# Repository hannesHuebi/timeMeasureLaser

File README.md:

# timeMeasureLaser
This is a repository for a time measuring device based on a laser and fotodiodes. This device was meant to measure the time small model boats needs to go 25m in a towing tank.

In this repository the Schematics and PCB design for the Arduinoshield is given as necessary Hardware for the time measuring equipment.

Additionaly the Arduino code is given which measures the time and provides the commands for the serial interface. 

Based on serial communication an excel-addin is is made which reads out the time and posts it in the excel-sheet. This ribbon/addin is availeble over COM-Interop to use it somerwhere else. This is mainly done to have an interface to VBA to generate buttons to start the time measuring.

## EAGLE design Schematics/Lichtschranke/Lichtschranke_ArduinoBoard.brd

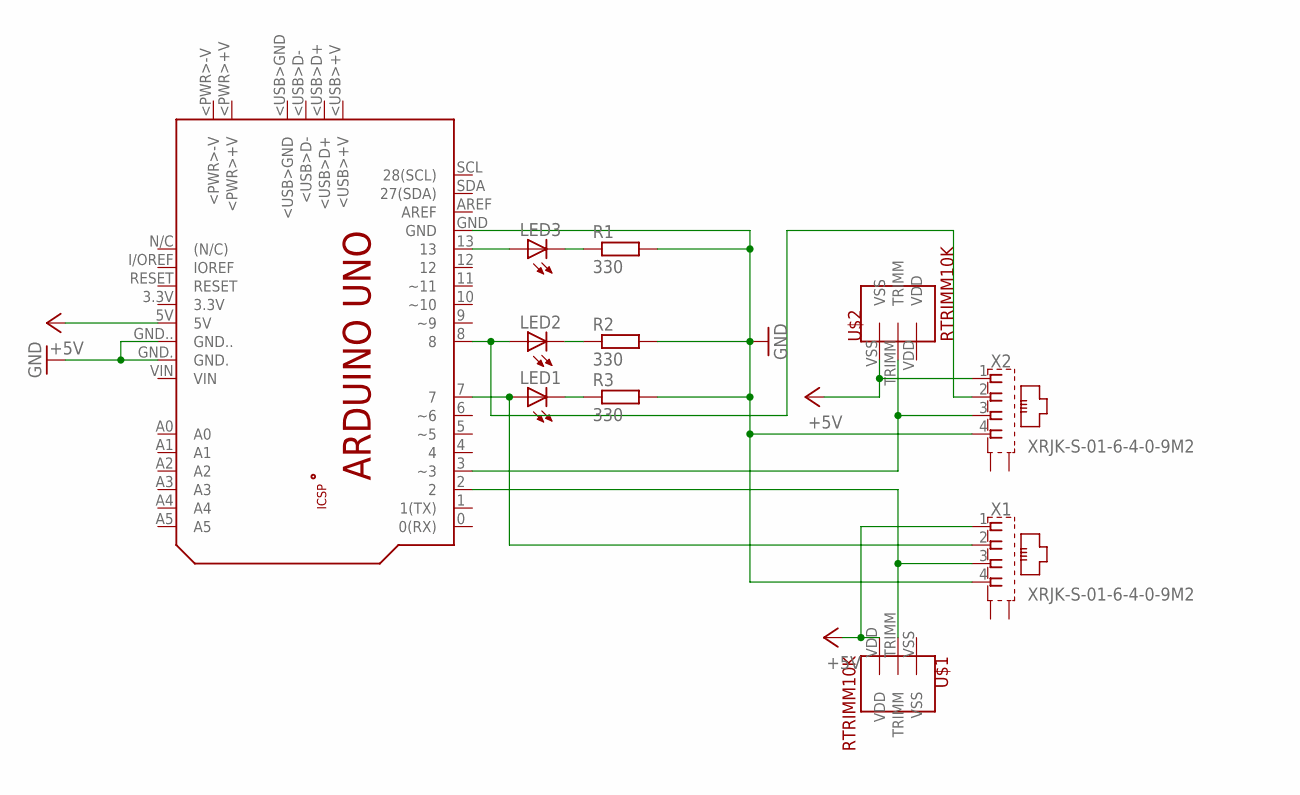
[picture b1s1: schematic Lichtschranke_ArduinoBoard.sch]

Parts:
LED1, LED2, LED3: LED5MM
PCB1: ARDUINO_UNO
R1, R2, R3: 330; 0411/12
U$1, U$2: RTRIMM10K
X1, X2: XRJK-S-01-6-4-0-9M2

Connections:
+5V: PCB1.5V, U$1.VDD, U$2.VSS, X1.1, X2.1
GND: PCB1.GND, PCB1.GND., PCB1.GND.., R1.2, R2.2, R3.2, X1.4, X2.4
unnamed: PCB1.3 (~3), U$2.TRIMM, X2.3
unnamed: LED1.A, PCB1.7, X1.2
unnamed: LED2.A, PCB1.8, X2.2
unnamed: PCB1.2, U$1.TRIMM, X1.3
unnamed: LED3.A, PCB1.13
unnamed: LED3.K (C), R1.1
unnamed: LED2.K (C), R2.1
unnamed: LED1.K (C), R3.1

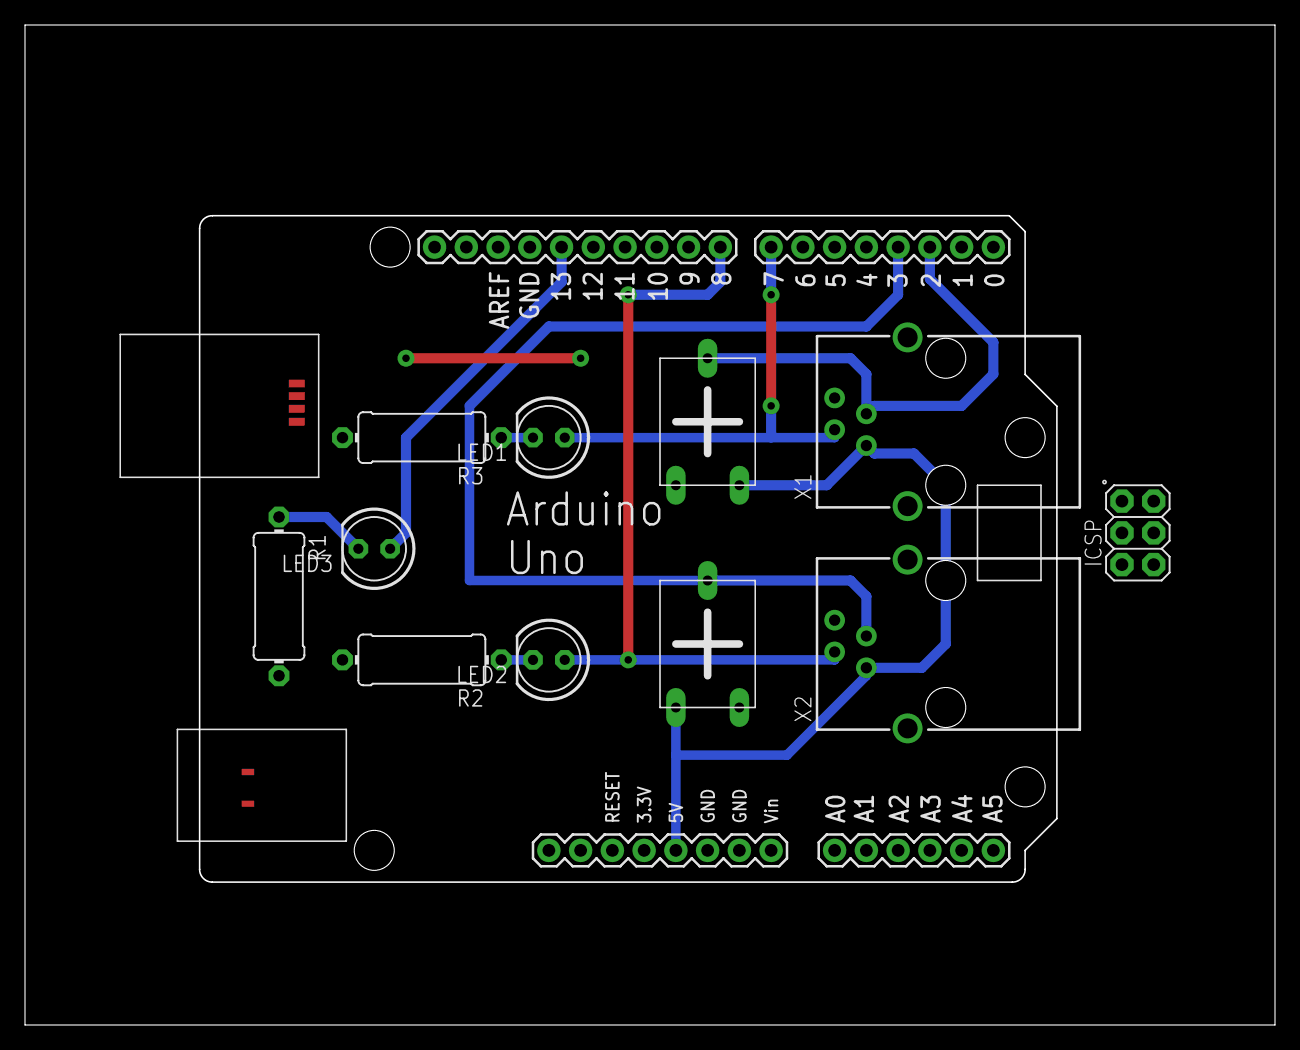
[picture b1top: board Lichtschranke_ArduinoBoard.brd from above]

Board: 2 copper layers, 100.0 x 80.0 mm, 11 parts (0 on the bottom side), 10 nets.

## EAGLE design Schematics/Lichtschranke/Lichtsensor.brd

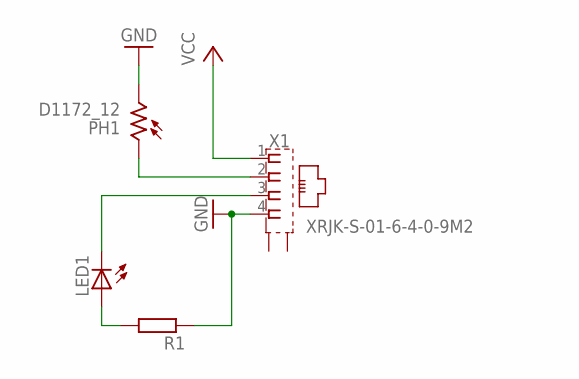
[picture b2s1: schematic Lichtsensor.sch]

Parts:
LED1: LED5MM
PH1: D1172_12; D11XX
R1: R-EU_0207/10; 0207/10
X1: XRJK-S-01-6-4-0-9M2

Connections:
GND: PH1.2, R1.1, X1.4
unnamed: PH1.1, X1.2
unnamed: LED1.K (C), X1.3
unnamed: LED1.A, R1.2
VCC: X1.1

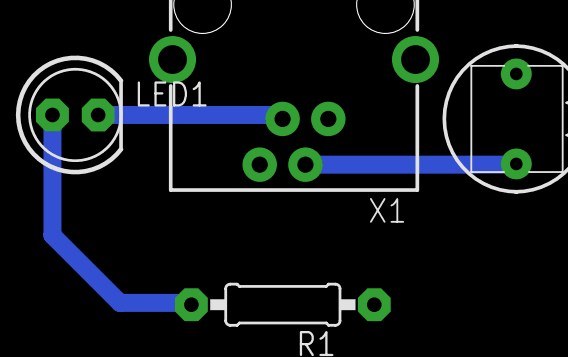
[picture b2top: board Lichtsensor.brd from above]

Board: 2 copper layers, 4 parts (0 on the bottom side), 4 nets.

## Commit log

2015-05-08 Test For RabbitVCS
2015-05-08 Added the Code for Microcontroller and Excel addin. also added the Excel file for time measuing
2015-05-08 Added Schematics for the sensors and boards
2015-05-08 Update README.md
    added a brief explanation of the repository
